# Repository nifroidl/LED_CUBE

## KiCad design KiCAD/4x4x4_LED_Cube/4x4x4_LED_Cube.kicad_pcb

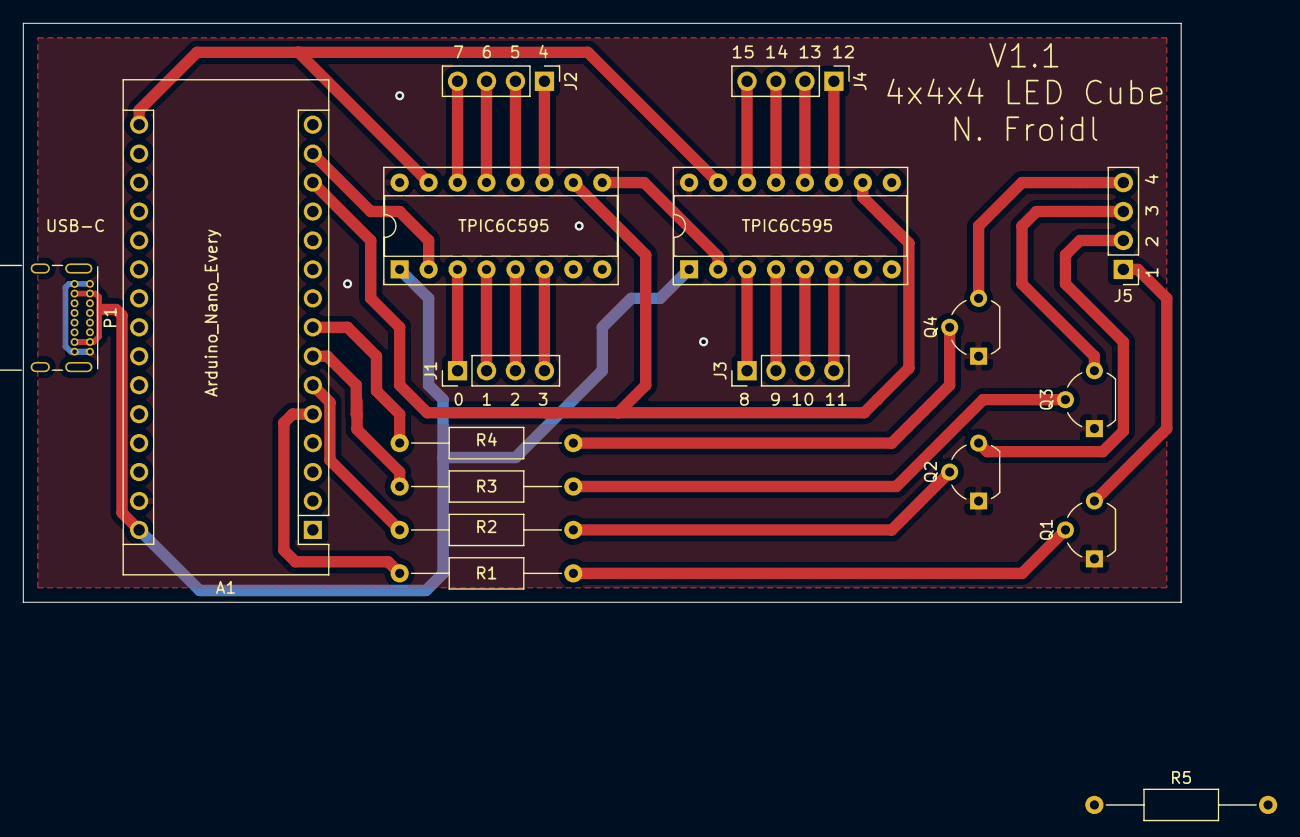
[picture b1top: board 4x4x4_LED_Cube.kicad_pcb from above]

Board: 2 copper layers, 101.6 x 50.8 mm, 18 parts (0 on the bottom side), 35 nets.

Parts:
A1: Arduino_Nano_Every; Arduino_Nano
J1, J2, J3, J4, J5: Conn_01x04_Male; PinHeader_1x04_P2.54mm_Vertical
P1: USB_C_Plug; USB_C_Receptacle_GCT_USB4085
Q1, Q2, Q3, Q4: 2N3904; TO-92_Wide
R1, R2, R3, R4: 1k; R_Axial_DIN0207_L6.3mm_D2.5mm_P15.24mm_Horizontal
R5: 330; R_Axial_DIN0207_L6.3mm_D2.5mm_P15.24mm_Horizontal
U1, U2: TPIC6C595N; DIP-16_W7.62mm_Socket

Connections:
+5V: A1.30, P1.A4, P1.A9, P1.B4, P1.B9, U1.1, U2.1
GND: A1.4, A1.29, P1.A1, P1.A12, P1.B1, P1.B12, R5.2, U1.16, U2.16
unnamed: A1.5, R1.2
unnamed: A1.6, R2.1
unnamed: A1.7, R3.1
unnamed: A1.8, R4.1
unnamed: A1.13, U1.10, U2.10
unnamed: A1.14, U1.2
unnamed: A1.16, U1.15, U2.15
unnamed: J1.1, U1.3
unnamed: J1.2, U1.4
unnamed: J1.3, U1.5
unnamed: J1.4, U1.6
unnamed: J2.1, U1.11
unnamed: J2.2, U1.12
unnamed: J2.3, U1.13
unnamed: J2.4, U1.14
unnamed: J3.1, U2.3
unnamed: J3.2, U2.4
unnamed: J3.3, U2.5
unnamed: J3.4, U2.6
unnamed: J4.1, U2.11
unnamed: J4.2, U2.12
unnamed: J4.3, U2.13
unnamed: J4.4, U2.14
unnamed: J5.1, Q1.3
unnamed: J5.2, Q2.3
unnamed: J5.3, Q3.3
unnamed: J5.4, Q4.3
unnamed: Q1.1, Q2.1, Q3.1, Q4.1, R5.1
unnamed: Q1.2, R1.1
unnamed: Q2.2, R2.2
unnamed: Q3.2, R3.2
unnamed: Q4.2, R4.2
unnamed: U1.9, U2.2

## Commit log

2021-12-19 Aedded KiCAD
